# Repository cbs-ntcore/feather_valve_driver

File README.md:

Feather compatible 16 channel valve driver.

This was designed for 12 volt Lee valves.

See [errata](/electronics/feather_valve_driver/ERRATA) for current minor electronic issues.

A simple 3d printed baseplate is included that supports the Lee valves:

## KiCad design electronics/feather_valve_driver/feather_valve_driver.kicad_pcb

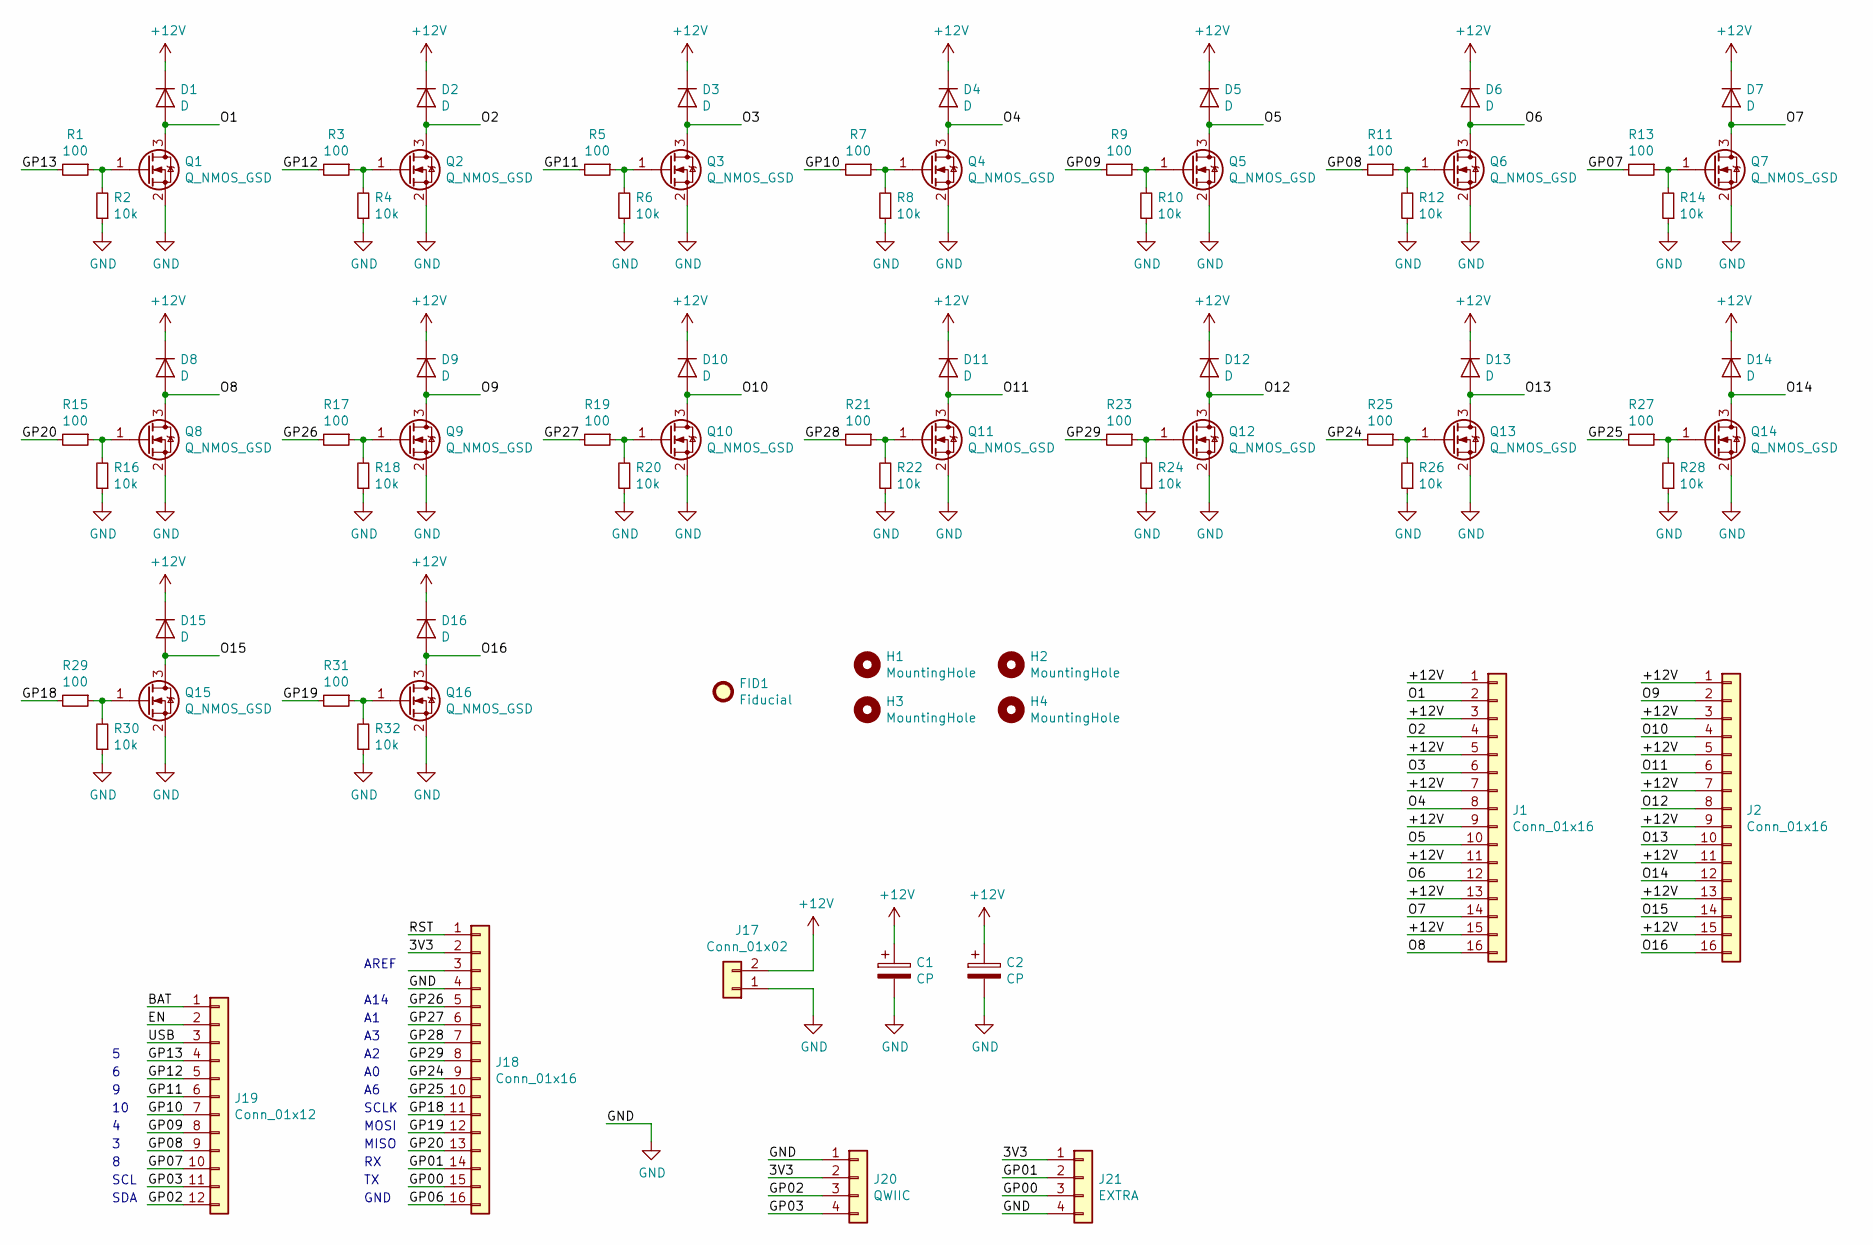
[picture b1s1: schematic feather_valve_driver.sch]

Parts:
C1, C2: CP; CP_Radial_D5.0mm_P2.00mm
D1, D2, D3, D4, D5, D6, D7, D8, D9, D10, D11, D12, D13, D14, D15, D16: D; D_SMA_Handsoldering
FID1: Fiducial; Fiducial_1.5mm_Mask3mm
H1, H2, H3, H4: MountingHole; MountingHole_3.2mm_M3
J1, J2: Conn_01x16; TerminalBlock_Phoenix_MKDS-1,5-16-5.08_1x16_P5.08mm_Horizon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
J17: Conn_01x02; TerminalBlock_TE_282834-2_1x02_P2.54mm_Horizontal
J18: Conn_01x16; PinHeader_1x16_P2.54mm_Vertical
J19: Conn_01x12; PinHeader_1x12_P2.54mm_Vertical
J20: QWIIC; JST_SH_BM04B-SRSS-TB_1x04-1MP_P1.00mm_Vertical
J21: EXTRA; PinHeader_1x04_P2.54mm_Vertical
Q1, Q2, Q3, Q4, Q5, Q6, Q7, Q8, Q9, Q10, Q11, Q12, Q13, Q14, Q15, Q16: Q_NMOS_GSD; SOT-23_Handsoldering
R1, R3, R5, R7, R9, R11, R13, R15, R17, R19, R21, R23, R25, R27, R29, R31: 100; R_0603_1608Metric_Pad1.05x0.95mm_HandSolder
R2, R4, R6, R8, R10, R12, R14, R16, R18, R20, R22, R24, R26, R28, R30, R32: 10k; R_0603_1608Metric_Pad1.05x0.95mm_HandSolder

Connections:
+12V: C1.1, C2.1, D1.1 (K), D2.1 (K), D3.1 (K), D4.1 (K), D5.1 (K), D6.1 (K), D7.1 (K), D8.1 (K), D9.1 (K), D10.1 (K), D11.1 (K), D12.1 (K), D13.1 (K), D14.1 (K), D15.1 (K), D16.1 (K), J1.1, J1.3, J1.5, J1.7, J1.9, J1.11, J1.13, J1.15, J2.1, J2.3, J2.5, J2.7, J2.9, J2.11, J2.13, J2.15, J17.2
/3V3: J18.2, J20.2, J21.1
/BAT: J19.1
/EN: J19.2
/GP00: J18.15, J21.3
/GP01: J18.14, J21.2
/GP02: J19.12, J20.3
/GP03: J19.11, J20.4
/GP06: J18.16
/GP07: J19.10, R13.2
/GP08: J19.9, R11.2
/GP09: J19.8, R9.2
/GP10: J19.7, R7.2
/GP11: J19.6, R5.2
/GP12: J19.5, R3.2
/GP13: J19.4, R1.2
/GP18: J18.11, R29.2
/GP19: J18.12, R31.2
/GP20: J18.13, R15.2
/GP24: J18.9, R25.2
/GP25: J18.10, R27.2
/GP26: J18.5, R17.2
/GP27: J18.6, R19.2
/GP28: J18.7, R21.2
/GP29: J18.8, R23.2
/O1: D1.2 (A), J1.2, Q1.3 (D)
/O2: D2.2 (A), J1.4, Q2.3 (D)
/O3: D3.2 (A), J1.6, Q3.3 (D)
/O4: D4.2 (A), J1.8, Q4.3 (D)
/O5: D5.2 (A), J1.10, Q5.3 (D)
/O6: D6.2 (A), J1.12, Q6.3 (D)
/O7: D7.2 (A), J1.14, Q7.3 (D)
/O8: D8.2 (A), J1.16, Q8.3 (D)
/O9: D9.2 (A), J2.2, Q9.3 (D)
/O10: D10.2 (A), J2.4, Q10.3 (D)
/O11: D11.2 (A), J2.6, Q11.3 (D)
/O12: D12.2 (A), J2.8, Q12.3 (D)
/O13: D13.2 (A), J2.10, Q13.3 (D)
/O14: D14.2 (A), J2.12, Q14.3 (D)
/O15: D15.2 (A), J2.14, Q15.3 (D)
/O16: D16.2 (A), J2.16, Q16.3 (D)
/RST: J18.1
/USB: J19.3
GND: C1.2, C2.2, J17.1, J18.4, J20.1, J21.4, Q1.2 (S), Q2.2 (S), Q3.2 (S), Q4.2 (S), Q5.2 (S), Q6.2 (S), Q7.2 (S), Q8.2 (S), Q9.2 (S), Q10.2 (S), Q11.2 (S), Q12.2 (S), Q13.2 (S), Q14.2 (S), Q15.2 (S), Q16.2 (S), R2.1, R4.1, R6.1, R8.1, R10.1, R12.1, R14.1, R16.1, R18.1, R20.1, R22.1, R24.1, R26.1, R28.1, R30.1, R32.1
unnamed: Q1.1 (G), R1.1, R2.2
unnamed: Q2.1 (G), R3.1, R4.2
unnamed: Q3.1 (G), R5.1, R6.2
unnamed: Q4.1 (G), R7.1, R8.2
unnamed: Q5.1 (G), R9.1, R10.2
unnamed: Q6.1 (G), R11.1, R12.2
unnamed: Q7.1 (G), R13.1, R14.2
unnamed: Q8.1 (G), R15.1, R16.2
unnamed: Q9.1 (G), R17.1, R18.2
unnamed: Q10.1 (G), R19.1, R20.2
unnamed: Q11.1 (G), R21.1, R22.2
unnamed: Q12.1 (G), R23.1, R24.2
unnamed: Q13.1 (G), R25.1, R26.2
unnamed: Q14.1 (G), R27.1, R28.2
unnamed: Q15.1 (G), R29.1, R30.2
unnamed: Q16.1 (G), R31.1, R32.2

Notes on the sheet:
SDA
SCL
GND
MISO
MOSI
SCLK
A14
AREF

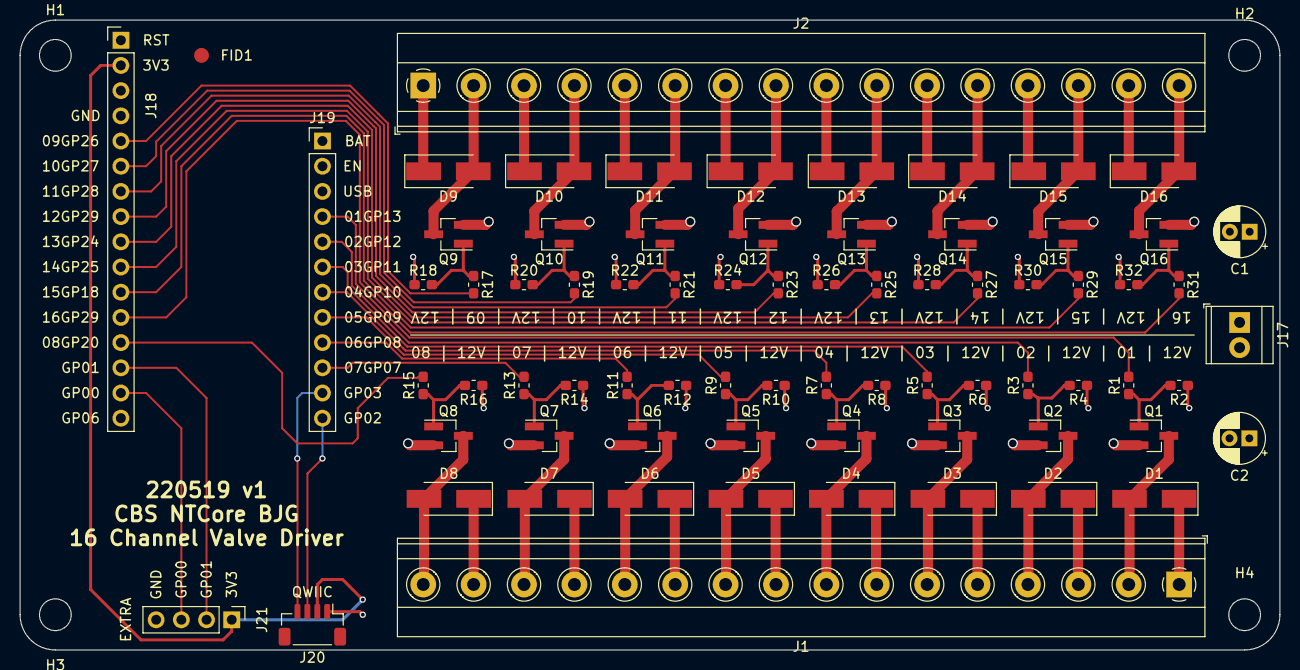
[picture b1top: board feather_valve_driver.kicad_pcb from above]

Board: 2 copper layers, 127.0 x 63.5 mm, 78 parts (0 on the bottom side), 55 nets.

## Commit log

2022-08-02 add 3d render to readme
2022-08-02 adding case, stl and render
